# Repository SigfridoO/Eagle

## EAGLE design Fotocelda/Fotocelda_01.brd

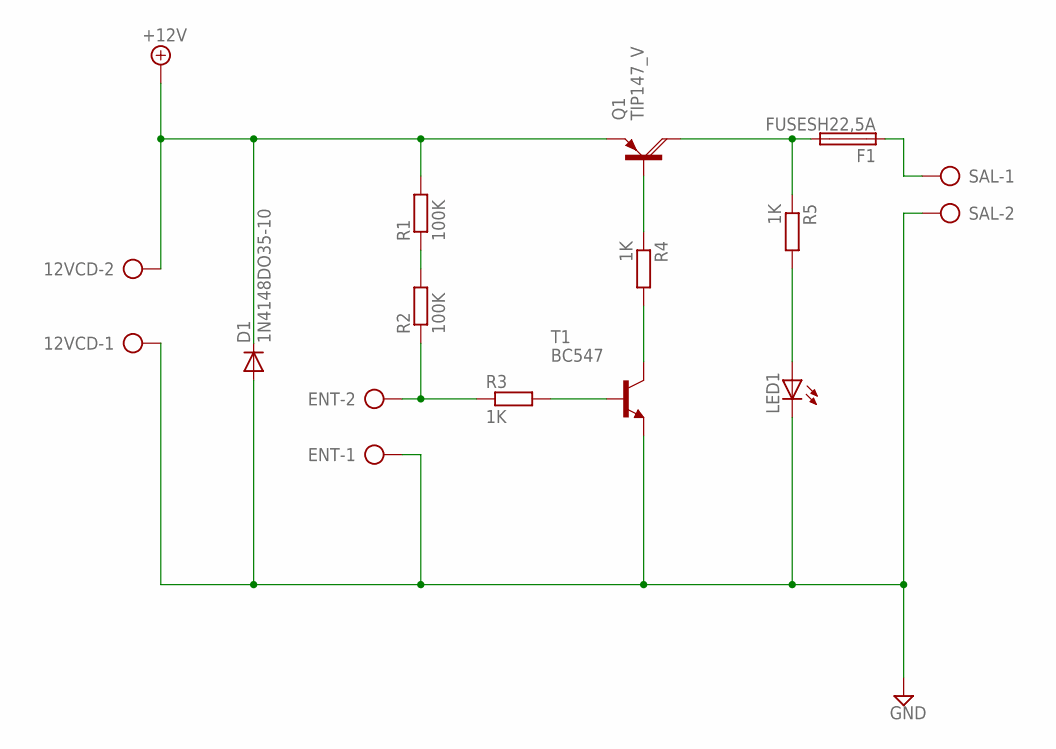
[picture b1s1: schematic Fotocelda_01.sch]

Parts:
12VCD: AK500/2
D1: 1N4148DO35-10; DO35-10
ENT: AK500/2
F1: FUSESH22,5A; SH22,5A
LED1: LED5MM
Q1: TIP147_V; SOT93V
R1, R2: 100K; 0207/10
R3, R4, R5: 1K; 0207/10
SAL: AK500/2
T1: BC547; TO92

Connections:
+12V: 12VCD.2, D1.C, Q1.E, R1.2
GND: 12VCD.1, D1.A, ENT.1, LED1.K (C), SAL.2, T1.1 (E)
unnamed: F1.1, SAL.1
unnamed: R1.1, R2.2
unnamed: ENT.2, R2.1, R3.1
unnamed: R3.2, T1.2 (B)
unnamed: R4.2, T1.3 (C)
unnamed: Q1.B, R4.1
unnamed: F1.2, Q1.C, R5.1
unnamed: LED1.A, R5.2

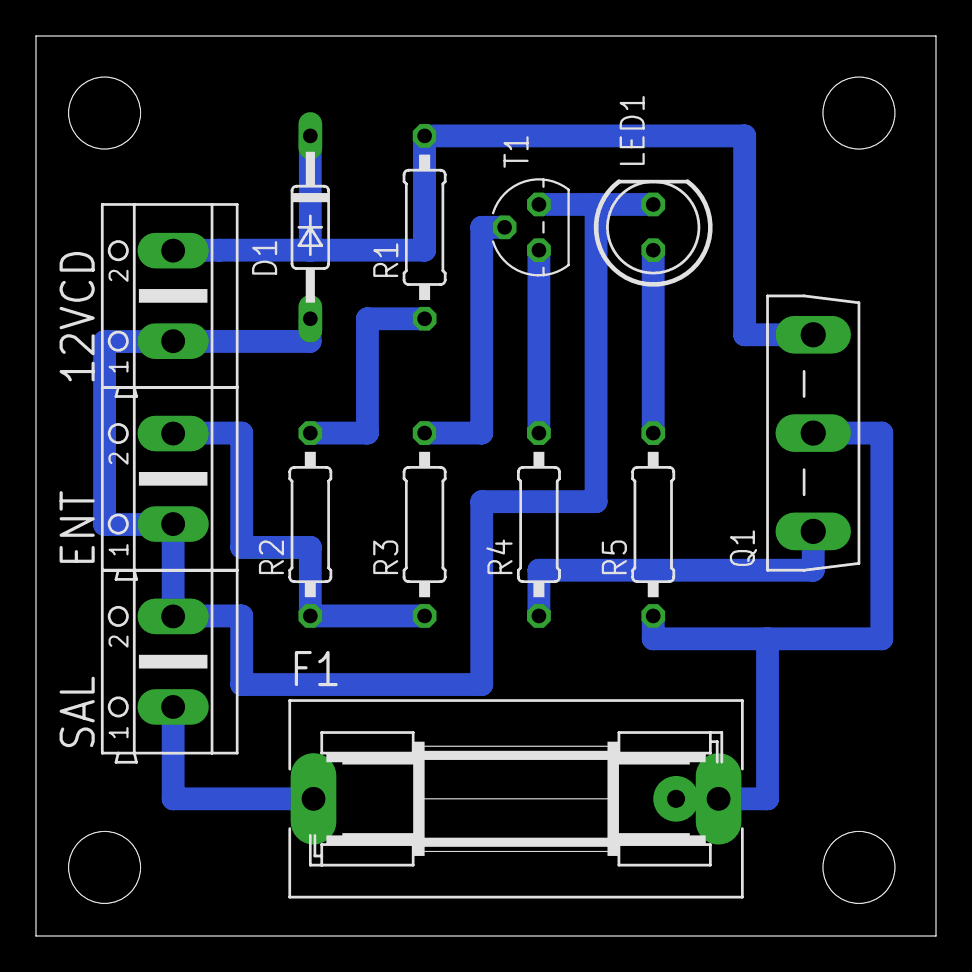
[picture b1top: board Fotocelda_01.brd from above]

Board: 2 copper layers, 50.0 x 50.0 mm, 13 parts (0 on the bottom side), 10 nets.

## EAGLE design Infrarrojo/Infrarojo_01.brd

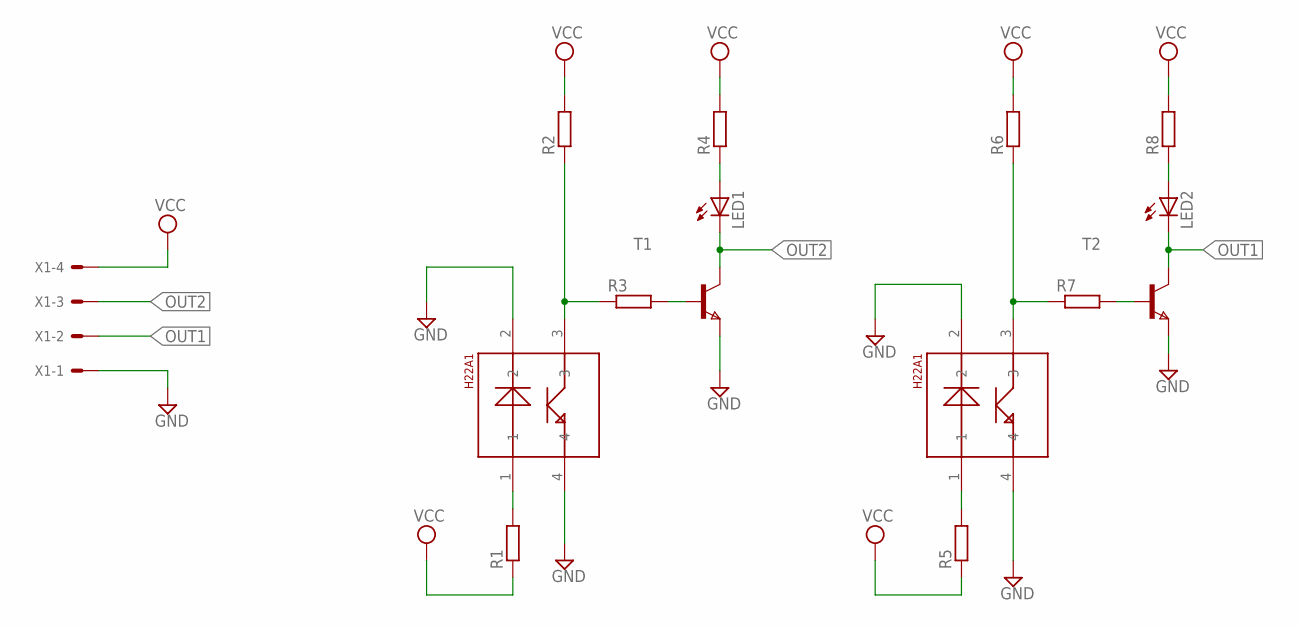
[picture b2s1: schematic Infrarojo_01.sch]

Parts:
IR1: IR1; H22A1
IR2: IR2; H22A1
LED1, LED2: LED3MM
R1, R2, R3, R4, R5, R6, R7, R8: R-EU_R0805; R0805
T1, T2: NPNSOT23; SOT-23
X1: C-GRID-04-70543; 70543-04

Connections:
GND: IR1.2, IR1.4, IR2.2, IR2.4, T1.2 (E), T2.2 (E), X1.1
unnamed: IR1.1, R1.2
unnamed: IR2.1, R5.2
unnamed: IR1.3, R2.1, R3.1
unnamed: R3.2, T1.3 (B)
unnamed: LED1.A, R4.1
unnamed: IR2.3, R6.1, R7.1
unnamed: R7.2, T2.3 (B)
unnamed: LED2.A, R8.1
OUT1: LED2.K (C), T2.1 (C), X1.2
OUT2: LED1.K (C), T1.1 (C), X1.3
VCC: R1.1, R2.2, R4.2, R5.1, R6.2, R8.2, X1.4

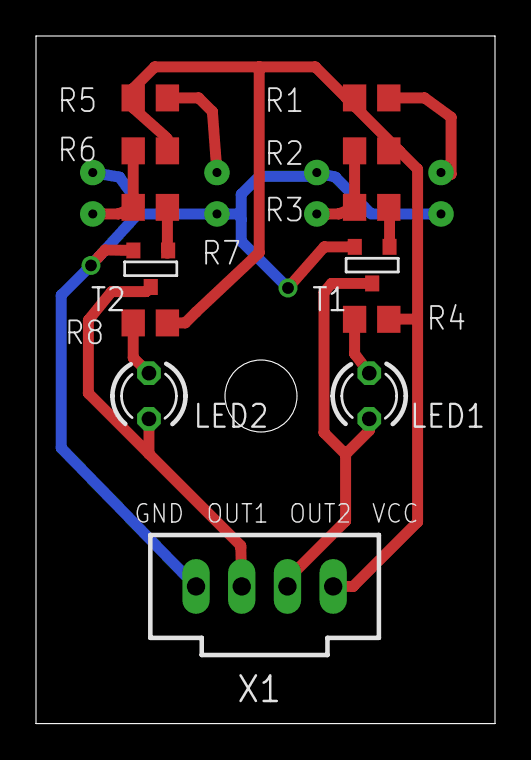
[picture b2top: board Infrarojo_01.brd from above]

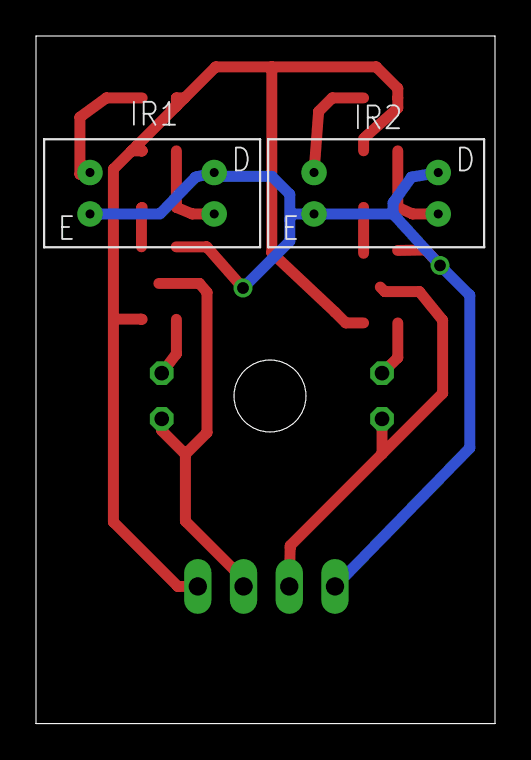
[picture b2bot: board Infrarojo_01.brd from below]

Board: 2 copper layers, 25.5 x 38.2 mm, 15 parts (2 on the bottom side), 12 nets.

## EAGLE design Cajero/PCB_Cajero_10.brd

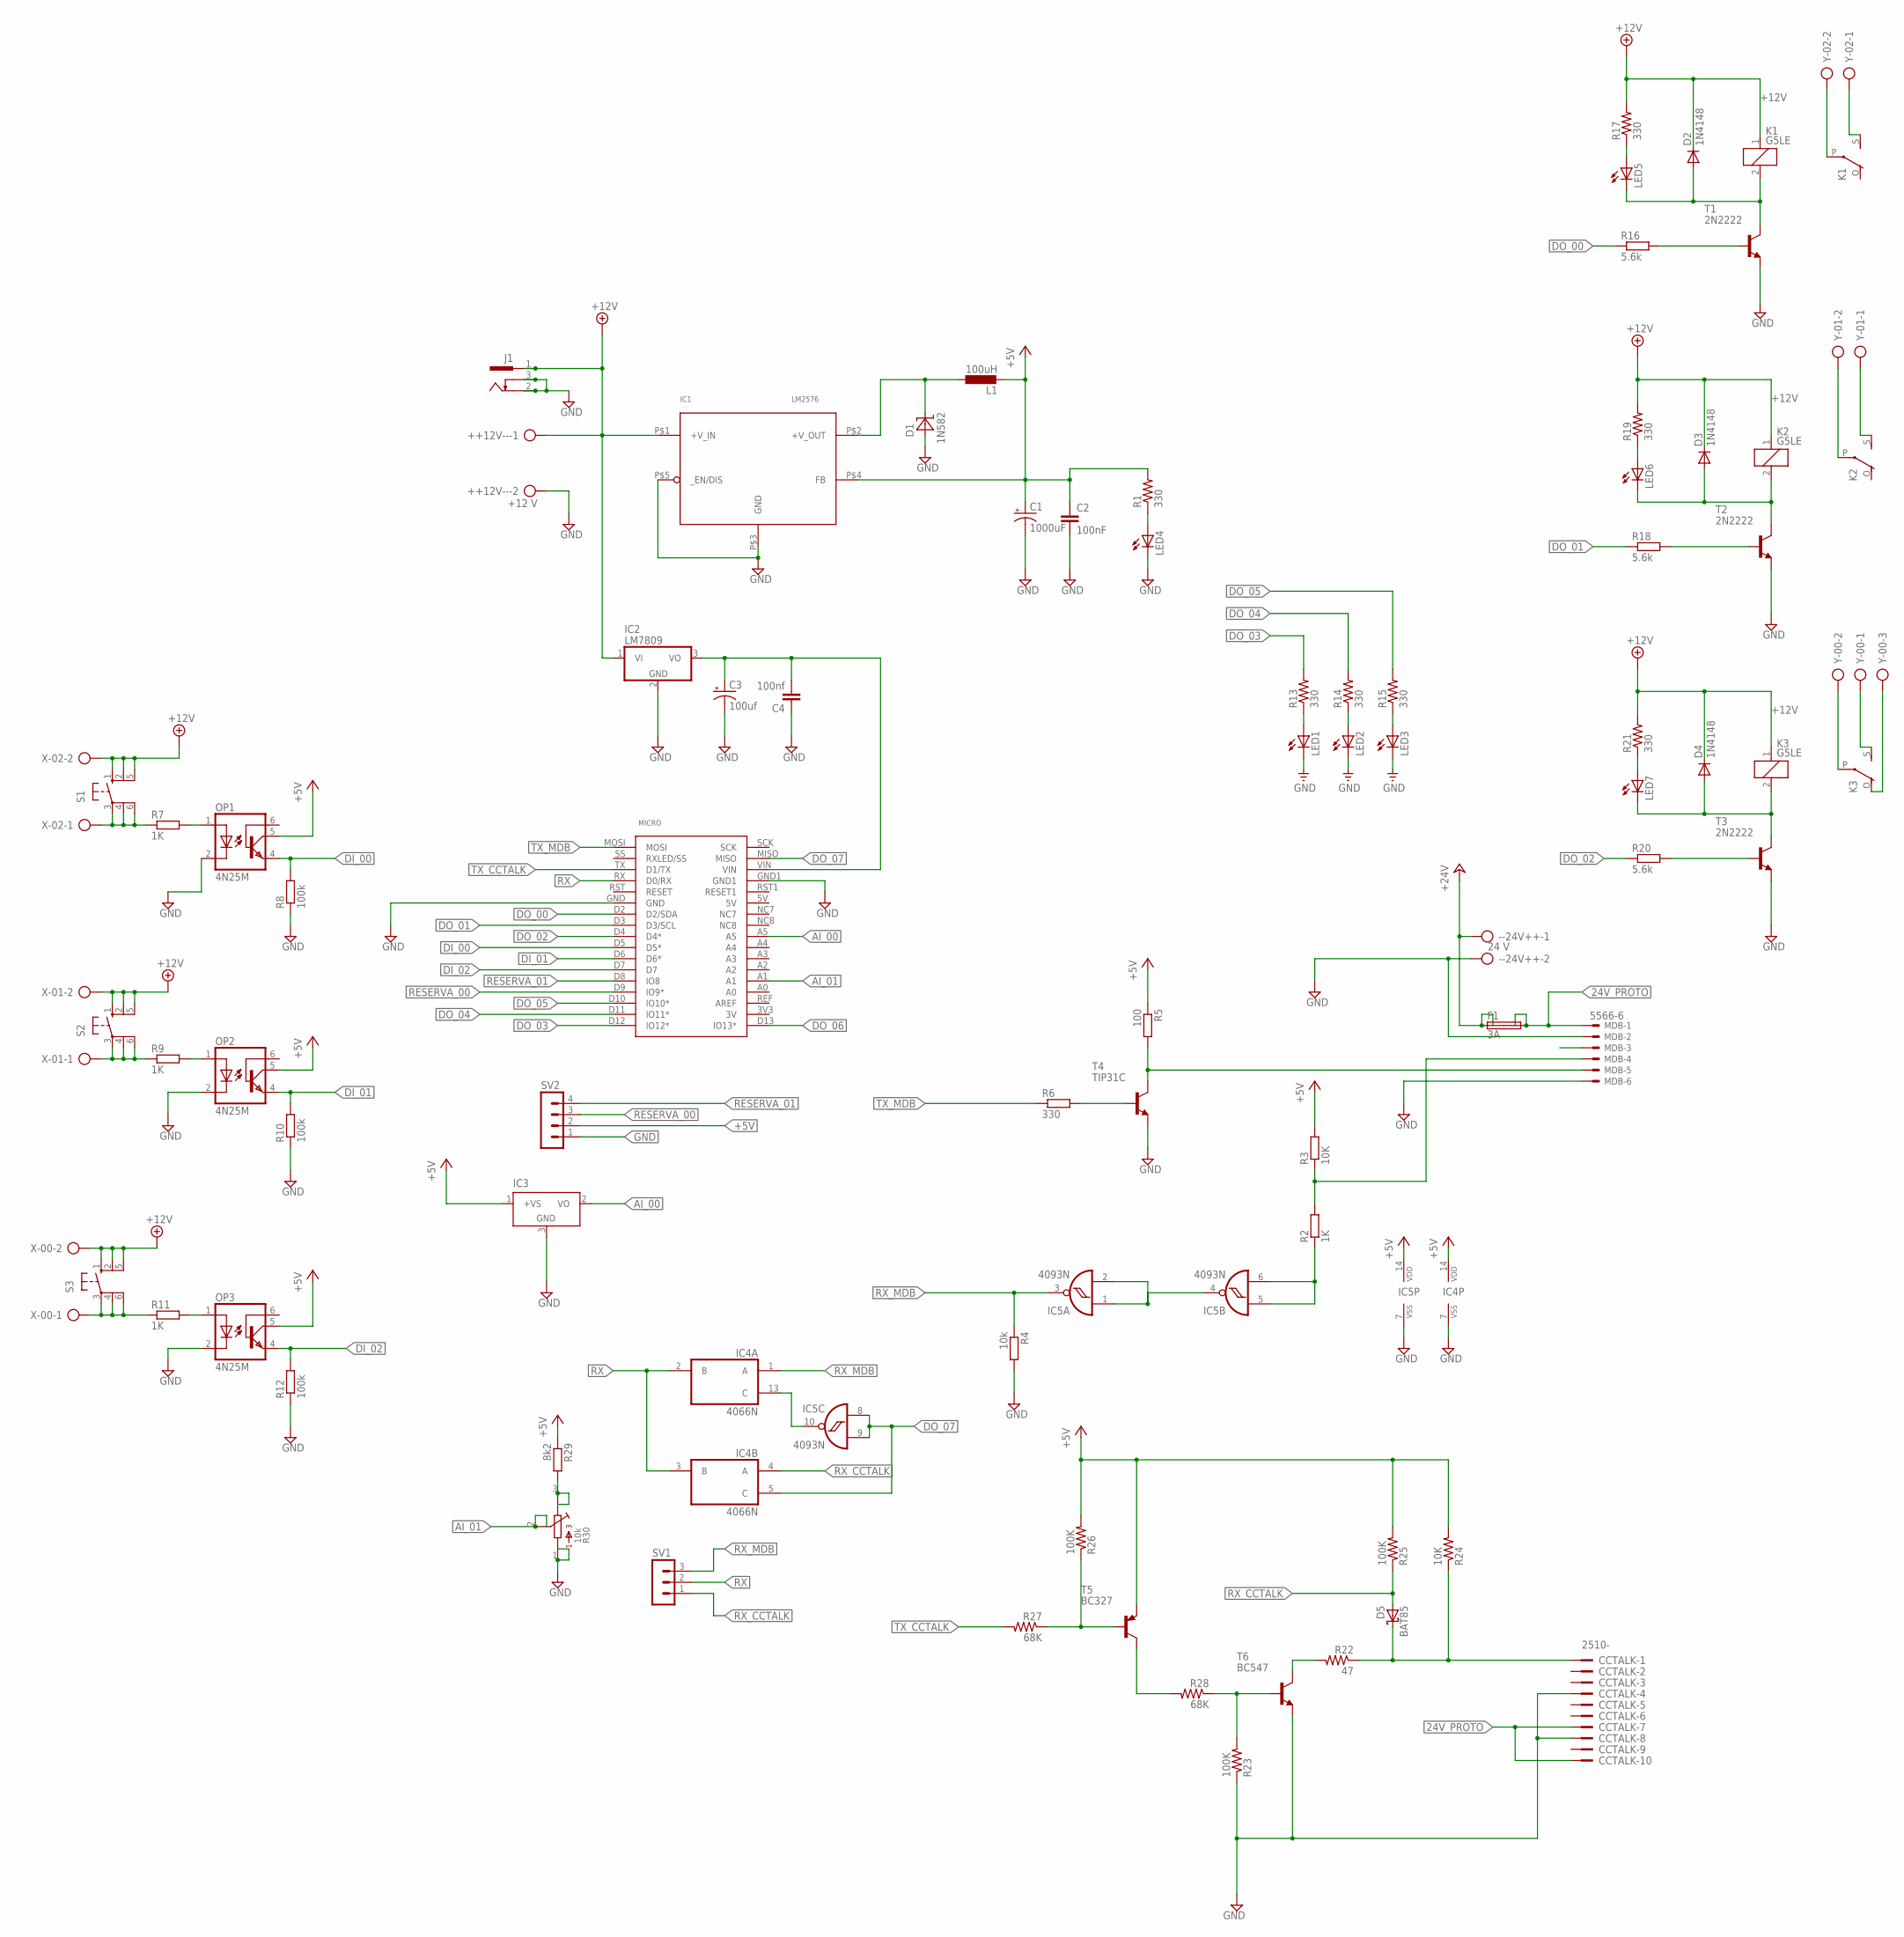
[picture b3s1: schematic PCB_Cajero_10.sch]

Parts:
++12V--: +12 V; AK500/2
--24V++: 24 V; AK500/2
C1: 1000uF; E5-5
C2: 100nF; C2.5-3
C3: 100uf; E2,5-6
C4: 100nf; C2.5-3
CCTALK: 2510-; PAK100/2500-10
D1: 1N582; 1N582*
D2, D3, D4: 1N4148; DO35-7
D5: BAT85; SOD68
F1: 3A; SHK20L
IC1: LM2576; TO220_SEP
IC2: LM7809; TO-220V
IC3: LM35CZ; TO92
IC4: 4066N; DIL14
IC5: 4093N; DIL14
J1: KLDVX-0202-A
K1, K2, K3: G5LE
L1: 100uH; DO3316P
LED1, LED2, LED3, LED4, LED5, LED6, LED7: LED5MM
MDB: 5566-6
MICRO: ARDUINO_MICROFOOTPRINT; ARDUINO-MICRO
OP1, OP2, OP3: 4N25M; DIL06
R1, R13, R14, R15, R17, R19, R21: 330; 0207/7
R2, R7, R9, R11: 1K; 0204/7
R3, R24: 10K; 0204/7
R4: 10k; 0204/7
R5: 100; 0309/10
R6: 330; 0204/7
R8, R10, R12: 100k; 0204/7
R16, R18, R20: 5.6k; 0204/7
R22: 47; 0204/7
R23, R25, R26: 100K; 0204/7
R27, R28: 68K; 0204/7
R29: 8k2; 0204/7
R30: 10k; 3386-MULTI
S1, S2, S3: 10-XX; B3F-10XX
SV1: MA03-1
SV2: MA04-1
T1, T2, T3: 2N2222; TO18
T4: TIP31C; TO-220V
T5: BC327; TO92
T6: BC547; TO92
X-00, X-01, X-02: AK500/2
Y-00: AK500/3
Y-01, Y-02: AK500/2

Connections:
24V_PROTO: CCTALK.7, CCTALK.10, F1.2A, F1.2B, MDB.1
+5V: C1.+, C2.1, IC1.P$4 (FB), IC3.1 (+VS), IC4.14 (VDD), IC5.14 (VDD), L1.1, OP1.5 (COL), OP2.5 (COL), OP3.5 (COL), R1.2, R3.2, R5.1, R24.2, R25.2, R26.2, R29.1, SV2.2, T5.1 (E)
+12V: ++12V--.1, D2.C, D3.C, D4.C, IC1.P$1 (+V_IN), IC2.1 (VI), J1.1, J1.1@1 (1), K1.1, K2.1, K3.1, R17.2, R19.2, R21.2, S1.1 (S), S1.2 (S1), S1.5 (S2), S2.1 (S), S2.2 (S1), S2.5 (S2), S3.1 (S), S3.2 (S1), S3.5 (S2), X-00.2, X-01.2, X-02.2
+24V: --24V++.1, F1.1A, F1.1B
AI_00: IC3.2 (VO), MICRO.A5
AI_01: MICRO.A1, R30.2, R30.5
DI_00: MICRO.D5 (D5*), OP1.4 (EMI), R8.2
DI_01: MICRO.D6 (D6*), OP2.4 (EMI), R10.2
DI_02: MICRO.D7, OP3.4 (EMI), R12.2
DO_00: MICRO.D2 (D2/SDA), R16.1
DO_01: MICRO.D3 (D3/SCL), R18.1
DO_02: MICRO.D4 (D4*), R20.1
DO_03: MICRO.D12 (IO12*), R13.2
DO_04: MICRO.D11 (IO11*), R14.2
DO_05: MICRO.D10 (IO10*), R15.2
DO_06: MICRO.D13 (IO13*)
DO_07: IC4.5 (C), IC5.8 (I0), IC5.9 (I1), MICRO.MISO
GND: ++12V--.2, --24V++.2, C1.-, C2.2, C3.-, C4.1, CCTALK.4, CCTALK.8, D1.A, IC1.P$3 (GND), IC1.P$5 (_EN/DIS), IC2.2 (GND), IC3.3 (GND), IC4.7 (VSS), IC5.7 (VSS), J1.2, J1.2@1 (2), J1.3, J1.3@1 (3), LED1.K (C), LED2.K (C), LED3.K (C), LED4.K (C), MDB.2, MDB.6, MICRO.GND, MICRO.GND1, OP1.2 (C), OP2.2 (C), OP3.2 (C), R4.2, R8.1, R10.1, R12.1, R23.1, R30.1, R30.4, SV2.1, T1.1 (E), T2.1 (E), T3.1 (E), T4.3 (E), T6.1 (E)
unnamed: C3.+, C4.2, IC2.3 (VO), MICRO.VIN
unnamed: R7.1, S1.3, S1.4 (P1), S1.6 (P2), X-02.1
unnamed: R9.1, S2.3, S2.4 (P1), S2.6 (P2), X-01.1
unnamed: D3.A, K2.2, LED6.K (C), T2.3 (C)
unnamed: K2.P, Y-01.2
unnamed: LED4.A, R1.1
unnamed: D1.C, IC1.P$2 (+V_OUT), L1.2
unnamed: LED5.A, R17.1
unnamed: OP1.1 (A), R7.2
unnamed: K2.S, Y-01.1
unnamed: LED1.A, R13.1
unnamed: LED2.A, R14.1
unnamed: LED3.A, R15.1
unnamed: R18.2, T2.2 (B)
unnamed: LED6.A, R19.1
unnamed: OP2.1 (A), R9.2
unnamed: R11.1, S3.3, S3.4 (P1), S3.6 (P2), X-00.1
unnamed: R29.2, R30.3, R30.6
unnamed: CCTALK.1, D5.C (K), R22.1, R24.1
unnamed: OP3.1 (A), R11.2
unnamed: R16.2, T1.2 (B)
unnamed: IC5.1 (I0), IC5.2 (I1), IC5.4 (O)
unnamed: D4.A, K3.2, LED7.K (C), T3.3 (C)
unnamed: D2.A, K1.2, LED5.K (C), T1.3 (C)
unnamed: K1.P, Y-02.2
unnamed: K1.S, Y-02.1
unnamed: R22.2, T6.3 (C)
unnamed: K3.P, Y-00.2
unnamed: R23.2, R28.1, T6.2 (B)
unnamed: R28.2, T5.3 (C)
unnamed: MDB.5, R5.2, T4.2 (C)
unnamed: R6.2, T4.1 (B)
unnamed: IC5.5 (I0), IC5.6 (I1), R2.1
unnamed: MDB.4, R2.2, R3.1
unnamed: K3.S, Y-00.1
unnamed: R26.1, R27.1, T5.2 (B)
unnamed: R20.2, T3.2 (B)
unnamed: LED7.A, R21.1
unnamed: IC4.13 (C), IC5.10 (O)
unnamed: K3.O, Y-00.3
RESERVA_00: MICRO.D9 (IO9*), SV2.3
RESERVA_01: MICRO.D8 (IO8), SV2.4
RX: IC4.2 (B), IC4.3 (B), MICRO.RX (D0/RX), SV1.2
RX_CCTALK: D5.A, IC4.4 (A), R25.1, SV1.1
RX_MDB: IC4.1 (A), IC5.3 (O), R4.1, SV1.3
TX_CCTALK: MICRO.TX (D1/TX), R27.2
TX_MDB: MICRO.MOSI, R6.1

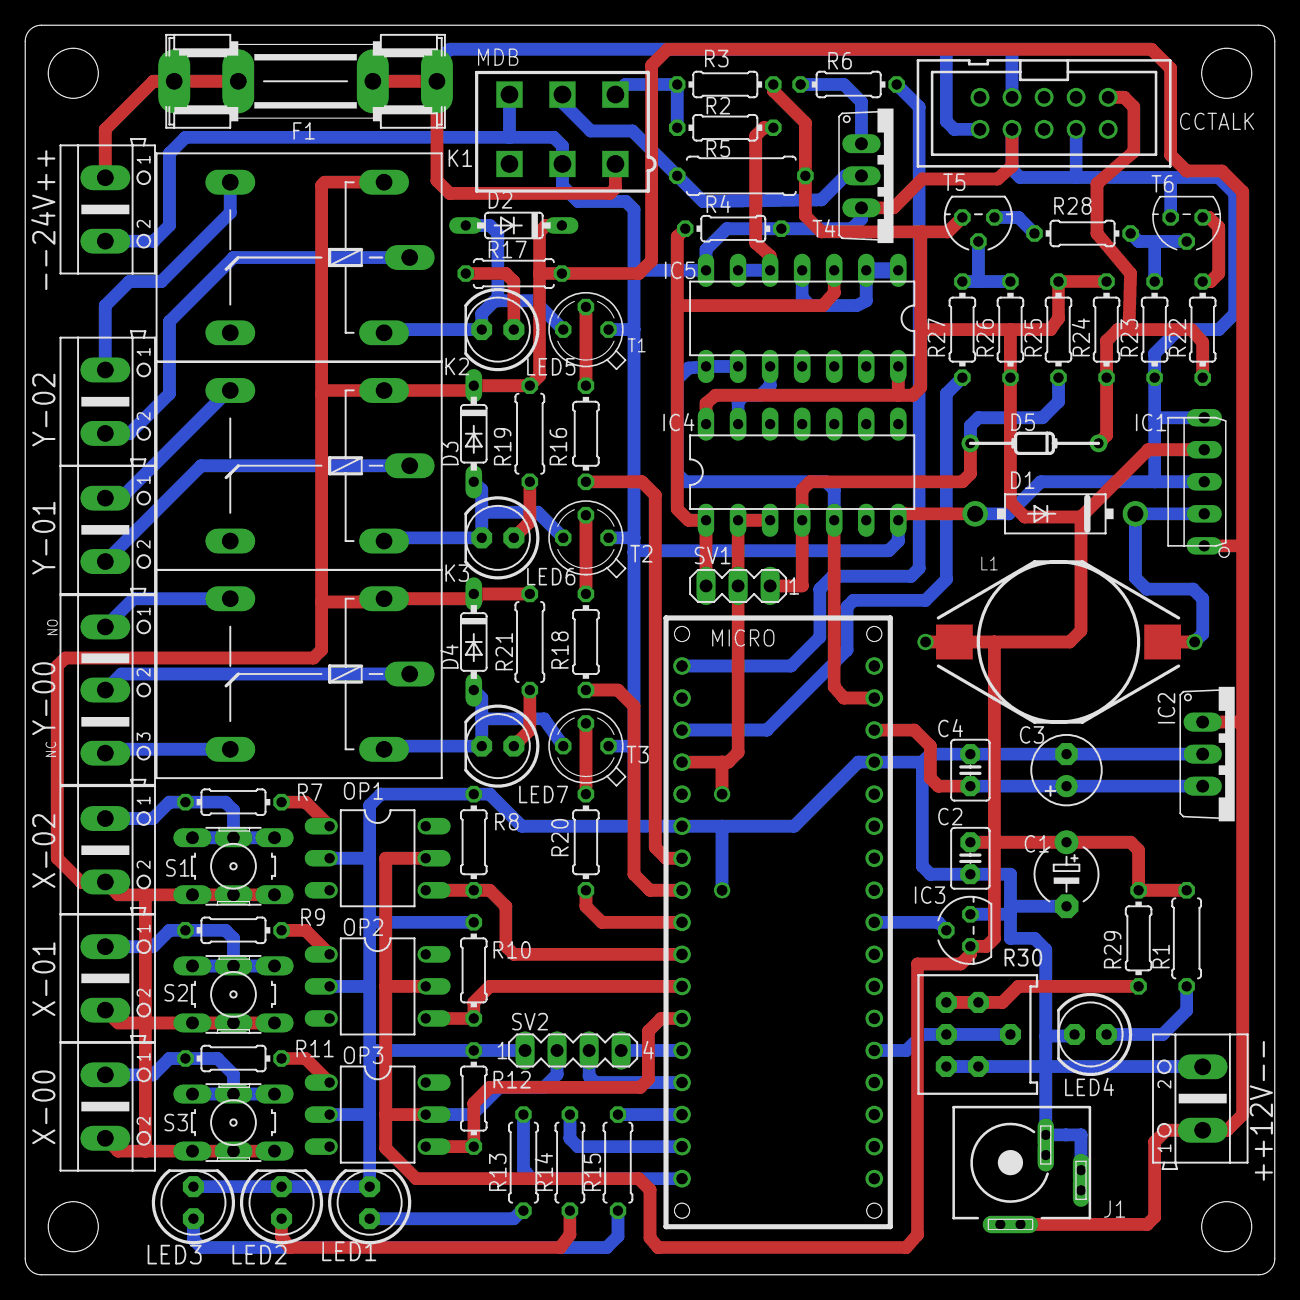
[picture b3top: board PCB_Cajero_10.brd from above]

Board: 2 copper layers, 99.1 x 99.1 mm, 82 parts (0 on the bottom side), 64 nets.

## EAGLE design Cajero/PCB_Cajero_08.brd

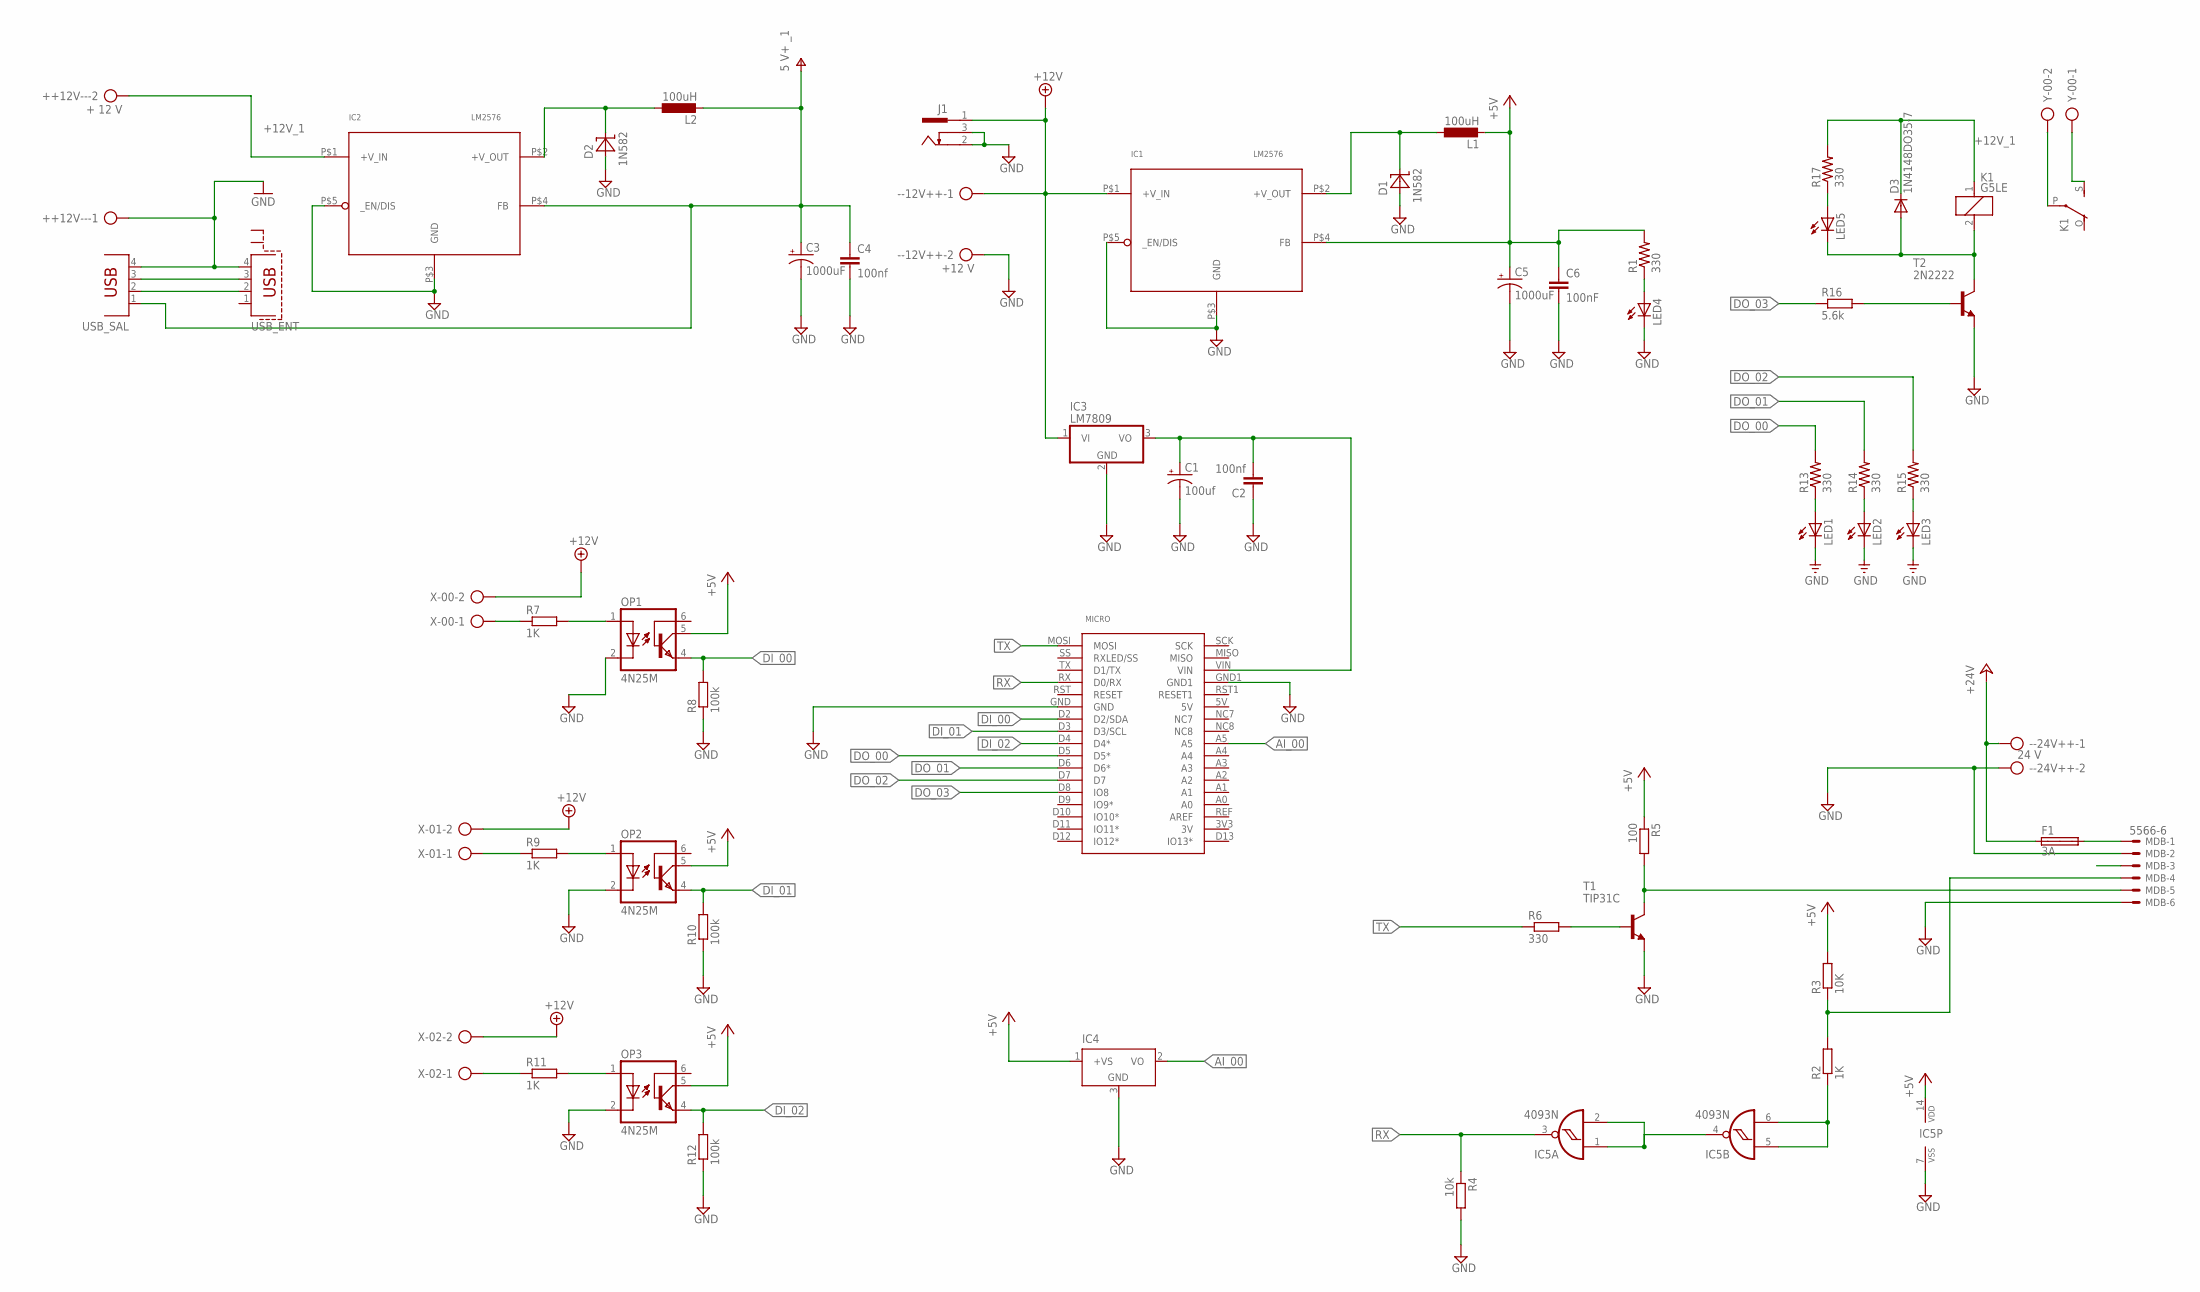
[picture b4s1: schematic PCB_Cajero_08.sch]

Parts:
++12V--: + 12 V; AK500/2
--12V++: +12 V; AK500/2
--24V++: 24 V; AK500/2
C1: 100uf; E2,5-6
C2, C4: 100nf; C2.5-3
C3, C5: 1000uF; E5-5
C6: 100nF; C2.5-3
D1, D2: 1N582; 1N582*
D3: 1N4148DO35-7; DO35-7
F1: 3A; SHK20L
IC1, IC2: LM2576; TO220_SEP
IC3: LM7809; TO-220V
IC4: LM35CZ; TO92
IC5: 4093N; DIL14
J1: KLDVX-0202-A
K1: G5LE
L1, L2: 100uH; DO3316P
LED1, LED2, LED3, LED4, LED5: LED5MM
MDB: 5566-6
MICRO: ARDUINO_MICROFOOTPRINT; ARDUINO-MICRO
OP1, OP2, OP3: 4N25M; DIL06
R1, R13, R14, R15, R17: 330; 0207/7
R2, R7, R9, R11: 1K; 0204/7
R3: 10K; 0204/7
R4: 10k; 0204/7
R5: 100; 0309/10
R6: 330; 0204/7
R8, R10, R12: 100k; 0204/7
R16: 5.6k; 0204/7
T1: TIP31C; TO-220V
T2: 2N2222; TO18
USB_ENT: PN61729-S
USB_SAL: PN87520
X-00, X-01, X-02: AK500/2
Y-00: AK500/2

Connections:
+5V: C5.+, C6.1, IC1.P$4 (FB), IC4.1 (+VS), IC5.14 (VDD), L1.1, OP1.5 (COL), OP2.5 (COL), OP3.5 (COL), R1.2, R3.2, R5.1
+12V: --12V++.1, IC1.P$1 (+V_IN), IC3.1 (VI), J1.1, X-00.2, X-01.2, X-02.2
+12V_1: ++12V--.2, D3.C, IC2.P$1 (+V_IN), K1.1, R17.2
+24V: --24V++.1, F1.1A
AI_00: IC4.2 (VO), MICRO.A5
DI_00: MICRO.D2 (D2/SDA), OP1.4 (EMI), R8.2
DI_01: MICRO.D3 (D3/SCL), OP2.4 (EMI), R10.2
DI_02: MICRO.D4 (D4*), OP3.4 (EMI), R12.2
DO_00: MICRO.D5 (D5*), R13.2
DO_01: MICRO.D6 (D6*), R14.2
DO_02: MICRO.D7, R15.2
DO_03: MICRO.D8 (IO8), R16.1
GND: ++12V--.1, --12V++.2, --24V++.2, C1.-, C2.1, C3.-, C4.2, C5.-, C6.2, D1.A, D2.A, IC1.P$3 (GND), IC1.P$5 (_EN/DIS), IC2.P$3 (GND), IC2.P$5 (_EN/DIS), IC3.2 (GND), IC4.3 (GND), IC5.7 (VSS), J1.2, J1.3, LED1.K (C), LED2.K (C), LED3.K (C), LED4.K (C), MDB.2, MDB.6, MICRO.GND, MICRO.GND1, OP1.2 (C), OP2.2 (C), OP3.2 (C), R4.2, R8.1, R10.1, R12.1, T1.3 (E), T2.1 (E), USB_ENT.4, USB_SAL.4
unnamed: C1.+, C2.2, IC3.3 (VO), MICRO.VIN
unnamed: R7.1, X-00.1
unnamed: R11.1, X-02.1
unnamed: USB_ENT.3, USB_SAL.3
unnamed: USB_ENT.2, USB_SAL.2
unnamed: F1.2A, MDB.1
unnamed: LED4.A, R1.1
unnamed: D1.C, IC1.P$2 (+V_OUT), L1.2
unnamed: LED5.A, R17.1
unnamed: OP1.1 (A), R7.2
unnamed: LED1.A, R13.1
unnamed: LED2.A, R14.1
unnamed: LED3.A, R15.1
unnamed: OP2.1 (A), R9.2
unnamed: R9.1, X-01.1
unnamed: OP3.1 (A), R11.2
unnamed: R16.2, T2.2 (B)
unnamed: IC5.1 (I0), IC5.2 (I1), IC5.4 (O)
unnamed: D3.A, K1.2, LED5.K (C), T2.3 (C)
unnamed: K1.P, Y-00.2
unnamed: K1.S, Y-00.1
unnamed: MDB.5, R5.2, T1.2 (C)
unnamed: R6.2, T1.1 (B)
unnamed: IC5.5 (I0), IC5.6 (I1), R2.1
unnamed: MDB.4, R2.2, R3.1
unnamed: D2.C, IC2.P$2 (+V_OUT), L2.2
RX: IC5.3 (O), MICRO.RX (D0/RX), R4.1
TX: MICRO.MOSI, R6.1
V+: C3.+, C4.1, IC2.P$4 (FB), L2.1, USB_SAL.1

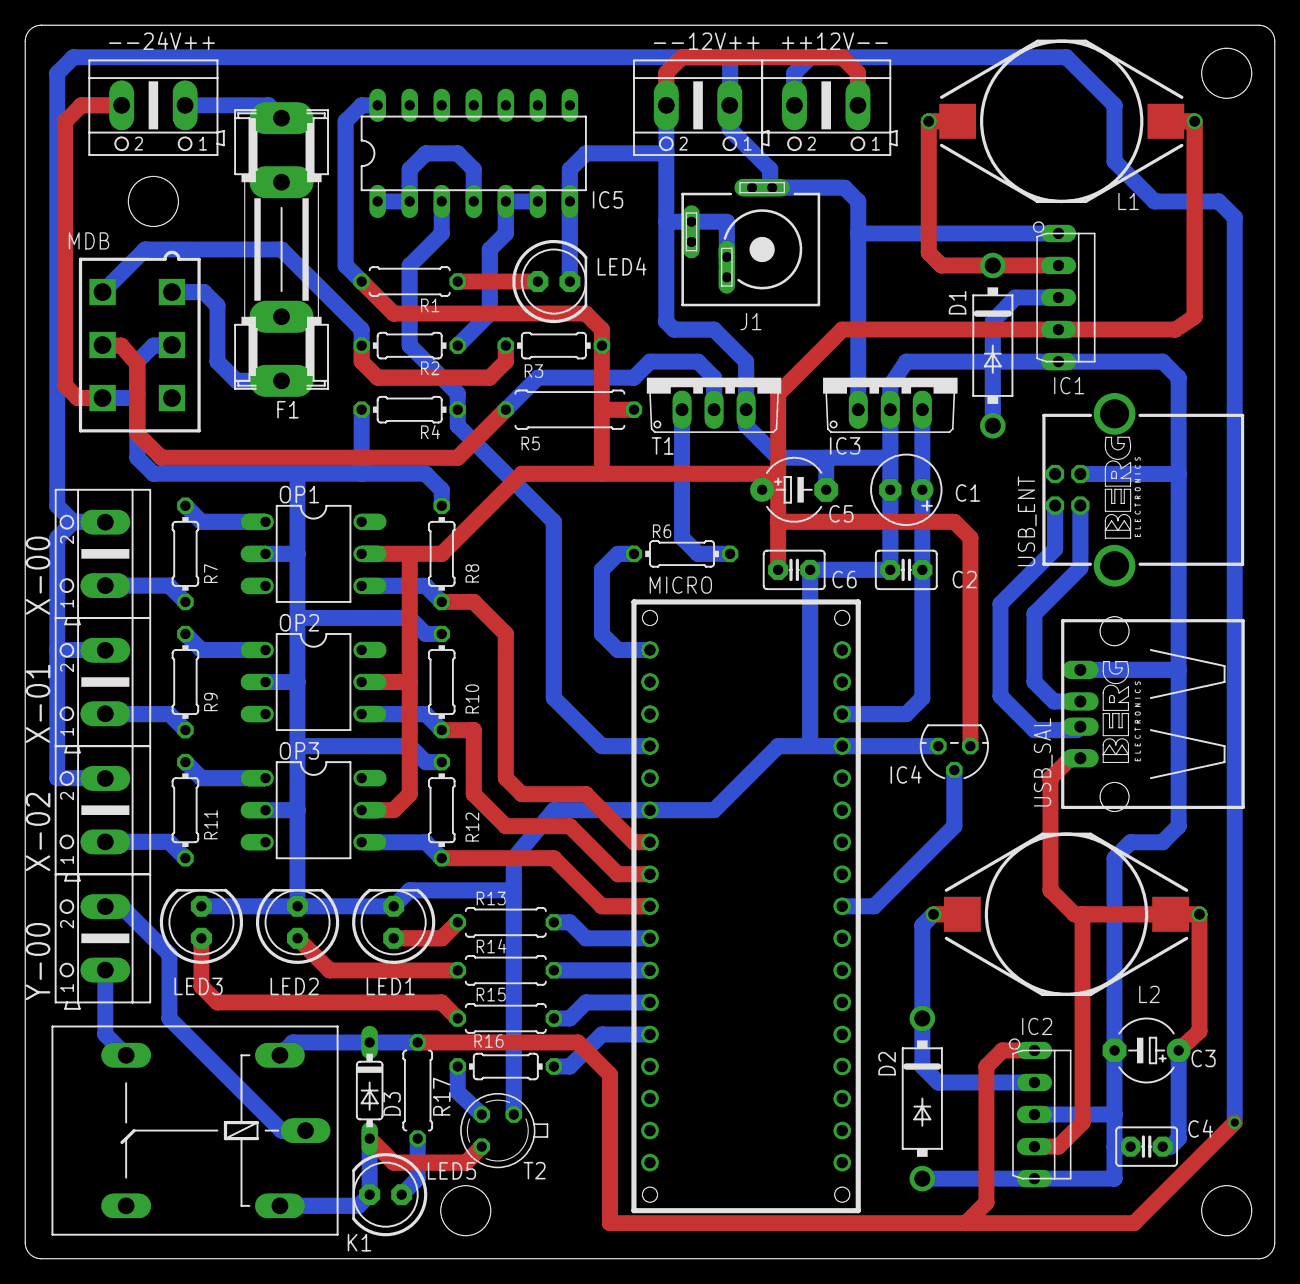
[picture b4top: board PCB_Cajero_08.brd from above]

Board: 2 copper layers, 99.1 x 97.8 mm, 57 parts (0 on the bottom side), 42 nets.

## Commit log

2019-08-29 Primer commit
